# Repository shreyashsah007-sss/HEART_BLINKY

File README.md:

# ❤️ Heart Blinky
### ABOUT
 I Made a Heart-shaped LED chaser PCB with custom artwork, powered by NE555 and CD4017. Designed in KiCad for Blueprint.
### **Why I Made This**
I finished my exams and had some free time, so I decided to jump back into another Blueprint project to keep improving my skills.
### **How to Use It**
Connect a 5V to 9V DC power source to the J1 header.

The LEDs will begin to chase in a heart-shaped sequence.

Turn the RV1 potentiometer knob to speed up or slow down the "heartbeat" effect.

### **3d view**

### **PCB**

### **schematic**

### ** Bill of Materials (BOM)**

| Designator                     | Value             | Footprint                                        |   Quantity |
|:-------------------------------|:------------------|:-------------------------------------------------|-----------:|
| D5,D9,D7,D8,D10,D6,D1,D3,D2,D4 | LED               | LED_D3.0mm                                       |         10 |
| RV1                            | 50k               | Potentiometer_Vishay_T93YA_Vertical              |          1 |
| R1                             | 1k                | R_Axial_DIN0207_L6.3mm_D2.5mm_P7.62mm_Horizontal |          1 |
| J1                             | Conn_01x02_Socket | PinHeader_1x02_P2.54mm_Vertical                  |          1 |
| C2                             | 0.01 uF           | C_Disc_D7.5mm_W2.5mm_P5.00mm                     |          1 |
| U2                             | 4017              | DIP-16_W7.62mm                                   |          1 |
| C1                             | 1 uF              | CP_Radial_D5.0mm_P2.00mm                         |          1 |
| R2                             | 470               | R_Axial_DIN0207_L6.3mm_D2.5mm_P7.62mm_Horizontal |          1 |
| U1                             | NE555P            | DIP-8_W7.62mm                                    |          1 |

[blinky.csv](https://github.com/user-attachments/files/25366329/blinky.csv)

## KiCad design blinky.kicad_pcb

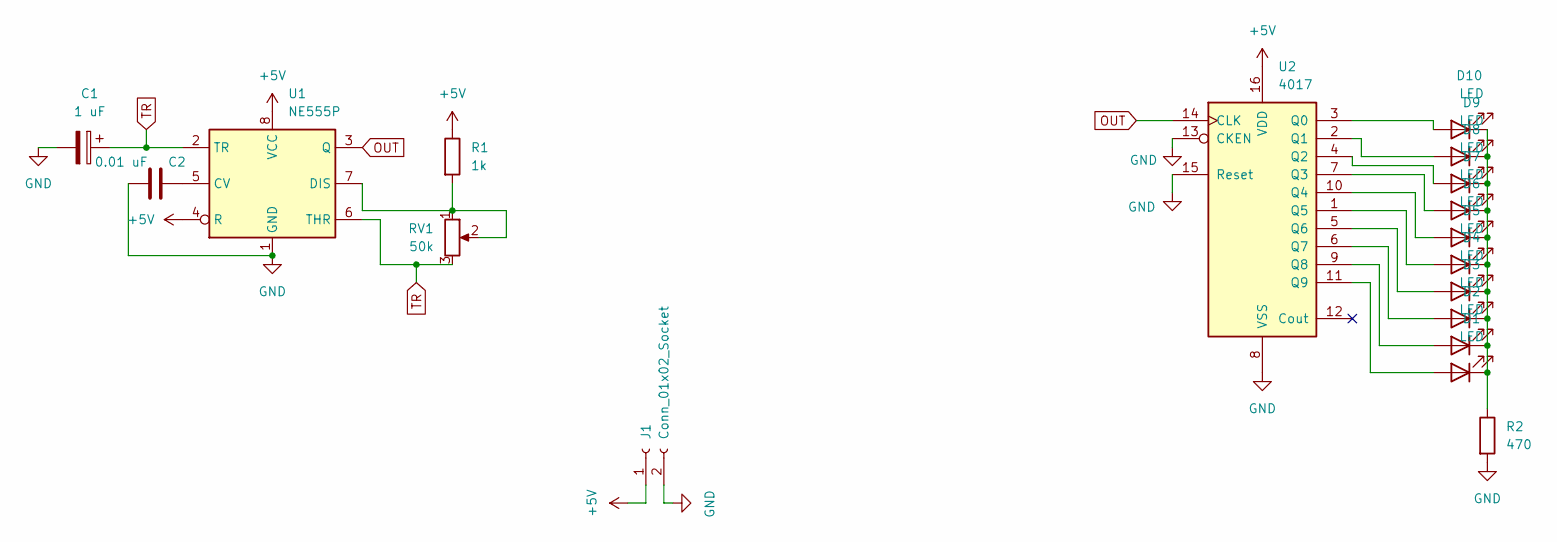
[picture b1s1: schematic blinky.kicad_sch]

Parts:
C1: 1 uF; CP_Radial_D5.0mm_P2.00mm
C2: 0.01 uF; C_Disc_D7.5mm_W2.5mm_P5.00mm
D1, D2, D3, D4, D5, D6, D7, D8, D9, D10: LED; LED_D3.0mm
J1: Conn_01x02_Socket; PinHeader_1x02_P2.54mm_Vertical
R1: 1k; R_Axial_DIN0207_L6.3mm_D2.5mm_P7.62mm_Horizontal
R2: 470; R_Axial_DIN0207_L6.3mm_D2.5mm_P7.62mm_Horizontal
RV1: 50k; Potentiometer_Vishay_T93YA_Vertical
U1: NE555P; DIP-8_W7.62mm
U2: 4017; DIP-16_W7.62mm

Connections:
+5V: J1.1, R1.1, U1.4 (R), U1.8 (VCC), U2.16 (VDD)
GND: C1.2, C2.1, J1.2, R2.2, U1.1 (GND), U2.8 (VSS), U2.13 (CKEN), U2.15 (Reset)
unnamed: D1.2 (A), U2.11 (Q9)
unnamed: D1.1 (K), D2.1 (K), D3.1 (K), D4.1 (K), D5.1 (K), D6.1 (K), D7.1 (K), D8.1 (K), D9.1 (K), D10.1 (K), R2.1
unnamed: D2.2 (A), U2.9 (Q8)
unnamed: D3.2 (A), U2.6 (Q7)
unnamed: D4.2 (A), U2.5 (Q6)
unnamed: D5.2 (A), U2.1 (Q5)
unnamed: D6.2 (A), U2.10 (Q4)
unnamed: D7.2 (A), U2.7 (Q3)
unnamed: D8.2 (A), U2.4 (Q2)
unnamed: D9.2 (A), U2.2 (Q1)
unnamed: D10.2 (A), U2.3 (Q0)
unnamed: C2.2, U1.5 (CV)
unnamed: R1.2, RV1.1, RV1.2, U1.7 (DIS)
OUT: U1.3 (Q), U2.14 (CLK)
TR: C1.1, RV1.3, U1.2 (TR), U1.6 (THR)

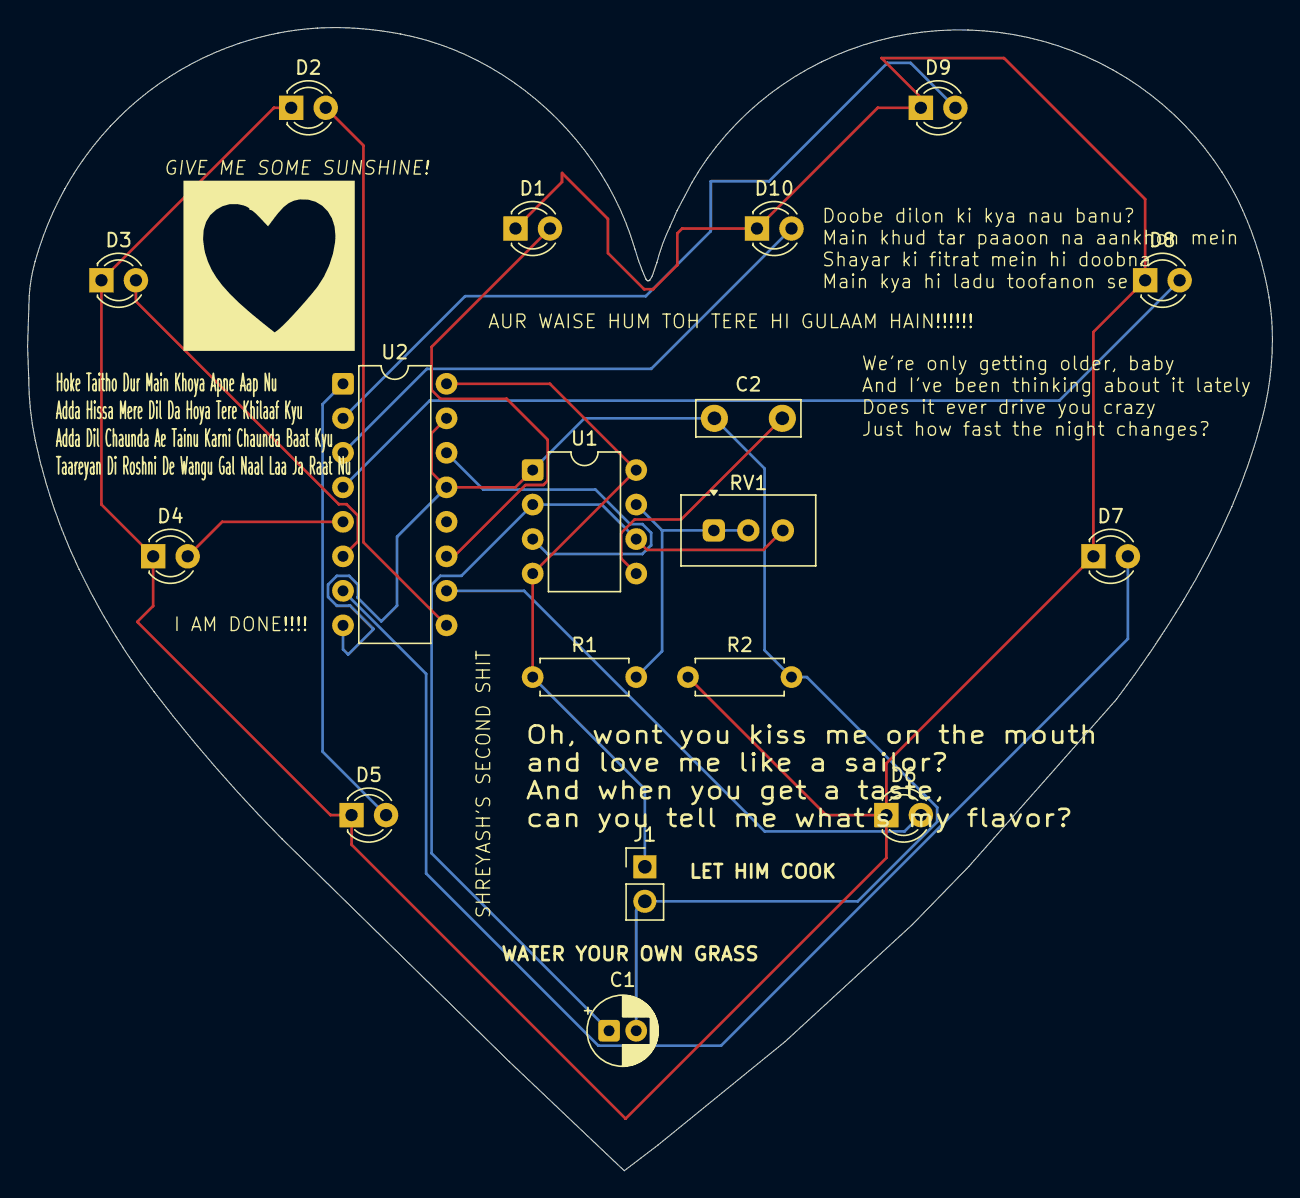
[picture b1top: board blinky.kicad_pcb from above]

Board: 2 copper layers, 91.6 x 84.2 mm, 20 parts (0 on the bottom side), 17 nets.

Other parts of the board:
               : LOGO; newig
                                                  : LOGO; gf111
